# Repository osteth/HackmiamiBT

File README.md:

# HackmiamiBT
A low cost Bluetooth pen testing suite

```sh
A python library for controling the FTDI chip
https://pypi.python.org/pypi/pyftdi/0.3.0
```

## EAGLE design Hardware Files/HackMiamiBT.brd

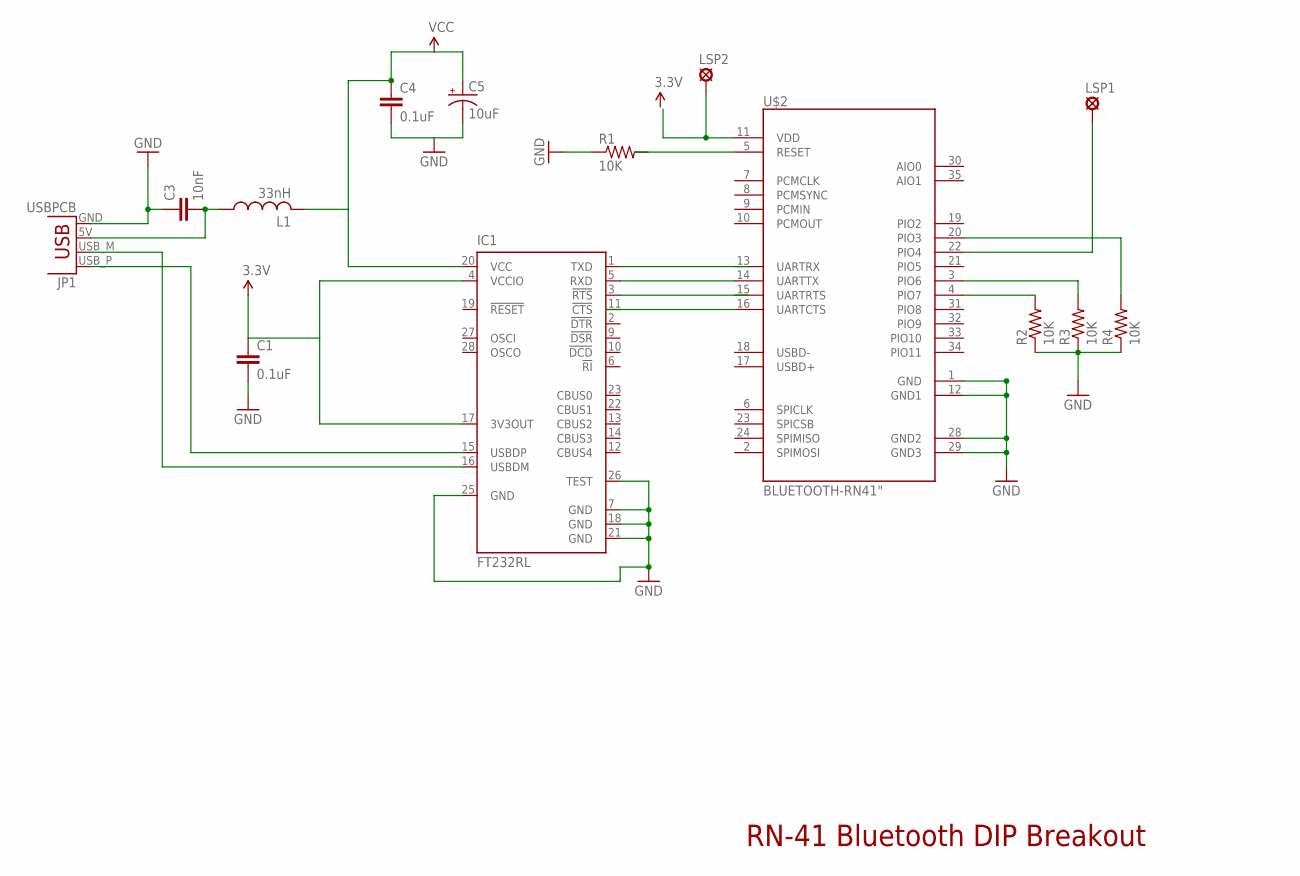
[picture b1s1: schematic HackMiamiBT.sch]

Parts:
C1, C4: 0.1uF; 0603-CAP
C3: 10nF; 0603-CAP
C5: 10uF; EIA3216
IC1: FT232RL; SSOP28
JP1: USBPCB; USB-A-PCB
L1: 33nH; L1812
LSP1, LSP2: MCS08
R1, R2, R3, R4: 10K; R0603
U$2: BLUETOOTH-RN41"; RN41

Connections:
GND: C1.2, C3.1, C4.2, C5.C (-), IC1.7 (GND), IC1.18 (GND), IC1.21 (GND), IC1.25 (GND), IC1.26 (TEST), JP1.GND, R1.1, R2.1, R3.1, R4.1, U$2.1 (GND), U$2.12 (GND1), U$2.28 (GND2), U$2.29 (GND3)
unnamed: R3.2, U$2.3 (PIO6)
unnamed: C3.2, JP1.5V (VBUS), L1.1
unnamed: LSP2.MP, U$2.11 (VDD)
unnamed: IC1.16 (USBDM), JP1.USB_M (D-)
unnamed: IC1.15 (USBDP), JP1.USB_P (D+)
unnamed: IC1.5 (RXD), U$2.14 (UARTTX)
unnamed: R2.2, U$2.4 (PIO7)
unnamed: LSP1.MP, U$2.22 (PIO4)
unnamed: R4.2, U$2.20 (PIO3)
VCC: C1.1, C4.1, C5.A (+), IC1.4 (VCCIO), IC1.17 (3V3OUT), IC1.20 (VCC), L1.2

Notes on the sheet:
RN-41 Bluetooth DIP Breakout

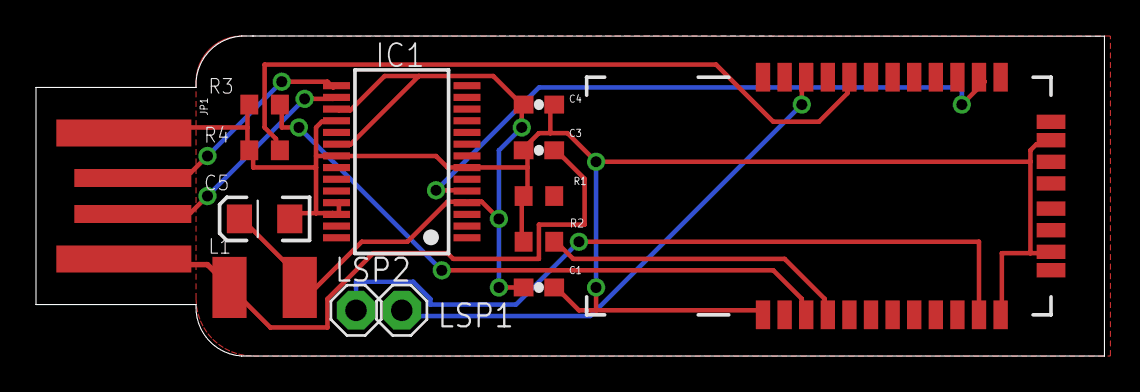
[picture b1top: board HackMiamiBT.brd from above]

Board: 2 copper layers, 59.4 x 17.8 mm, 14 parts (0 on the bottom side), 11 nets.

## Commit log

2015-05-31 Initial Hardware Design files
2015-05-31 adding documentation
2015-05-31 add doc
2015-06-03 added documentation
    added documentation
2015-06-21 changed readme
2015-06-21 change readme

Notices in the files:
parts and their libraries:
SparkFun-Connectors: Licensing: Creative Commons ShareAlike 4.0 International - https://creativecommons.org/licenses/by-sa/4.0
